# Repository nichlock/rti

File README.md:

# Open Source RTI

Source for the software, hardware and physical construction of a Reflectance Transformation Imager for George Washington University.

For information on the contents of the system, see [our Wiki](https://github.com/nichlock/rti/wiki). For more on the build and usage, [see the docs folder](../../tree/master/docs).

This repository contains our RTI's hardware and software implementation, and includes the source and documentation for:
1. A custom designed Arduino Mega shield to control the dome, which powers a three-color LED matrix and triggers the cameras.
2. Another custom circuit board which holds all three colors of LEDs in a smaller area than if we had three separate boards, allowing for a more compact dome.
3. The program to control the dome, with a serial or GUI control interface.
4. The GUI within the above program, which enables easy control over the whole system with no need for technical knowledge. See more about the GUI on our [system overview page](https://github.com/nichlock/rti/wiki/About-the-System#software-and-gui).

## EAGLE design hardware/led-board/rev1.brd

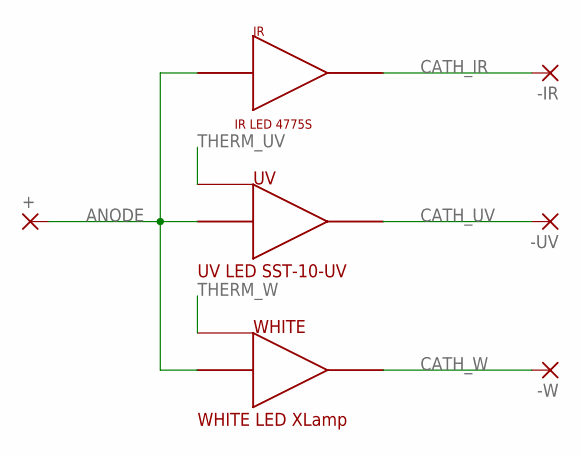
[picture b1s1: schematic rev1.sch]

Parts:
+: SMD5; SMD2,54-5,08
-IR: SMD5; SMD2,54-5,08
-UV: SMD5; SMD2,54-5,08
-W: SMD5; SMD2,54-5,08
IR: 4775S
UV: SST-10-UV; LED
WHITE: XLAMPXPG2; LED

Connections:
ANODE: +.1, IR.ANODE, IR.ANODE1 (ANODE), IR.ANODE2 (ANODE), UV.ANODE, WHITE.ANODE
CATH_IR: -IR.1, IR.CATHODE, IR.CATHODE1 (CATHODE)
CATH_UV: -UV.1, UV.CATHODE
CATH_W: -W.1, WHITE.CATHODE
THERM_UV: UV.THERM
THERM_W: WHITE.THERM

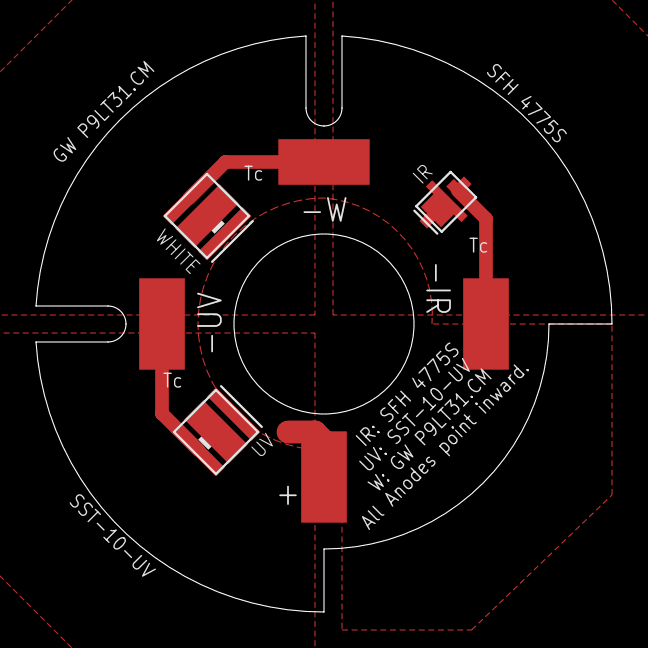
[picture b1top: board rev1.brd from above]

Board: 2 copper layers, 32.0 x 32.0 mm, 7 parts (0 on the bottom side), 4 nets.

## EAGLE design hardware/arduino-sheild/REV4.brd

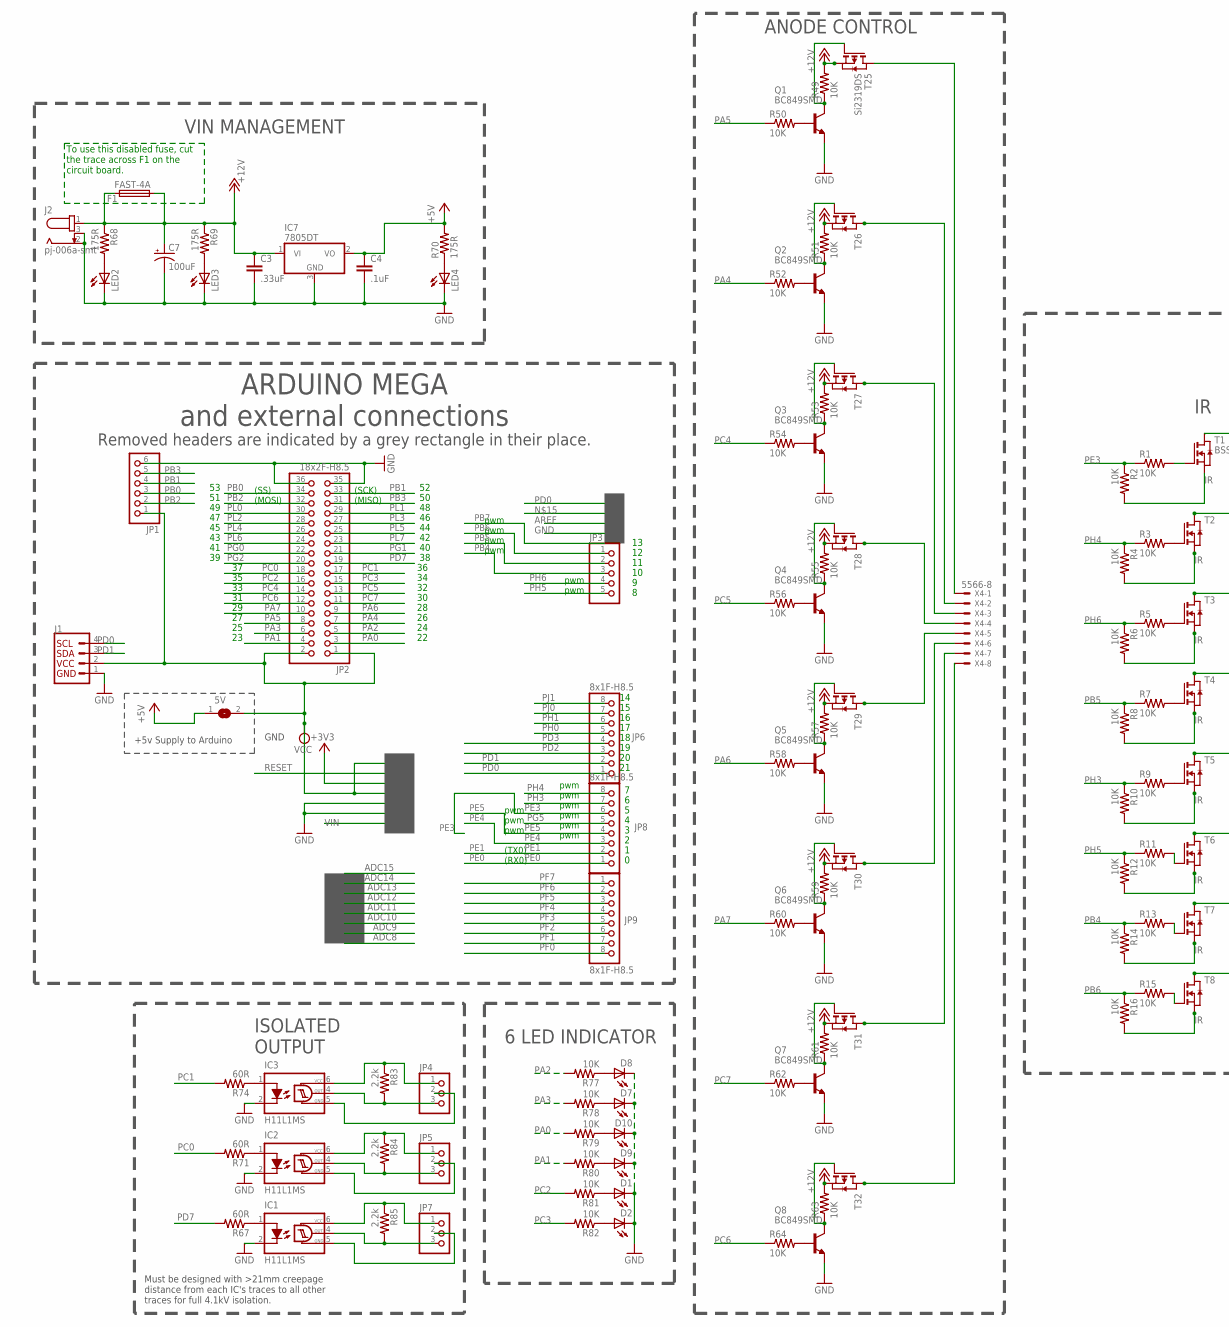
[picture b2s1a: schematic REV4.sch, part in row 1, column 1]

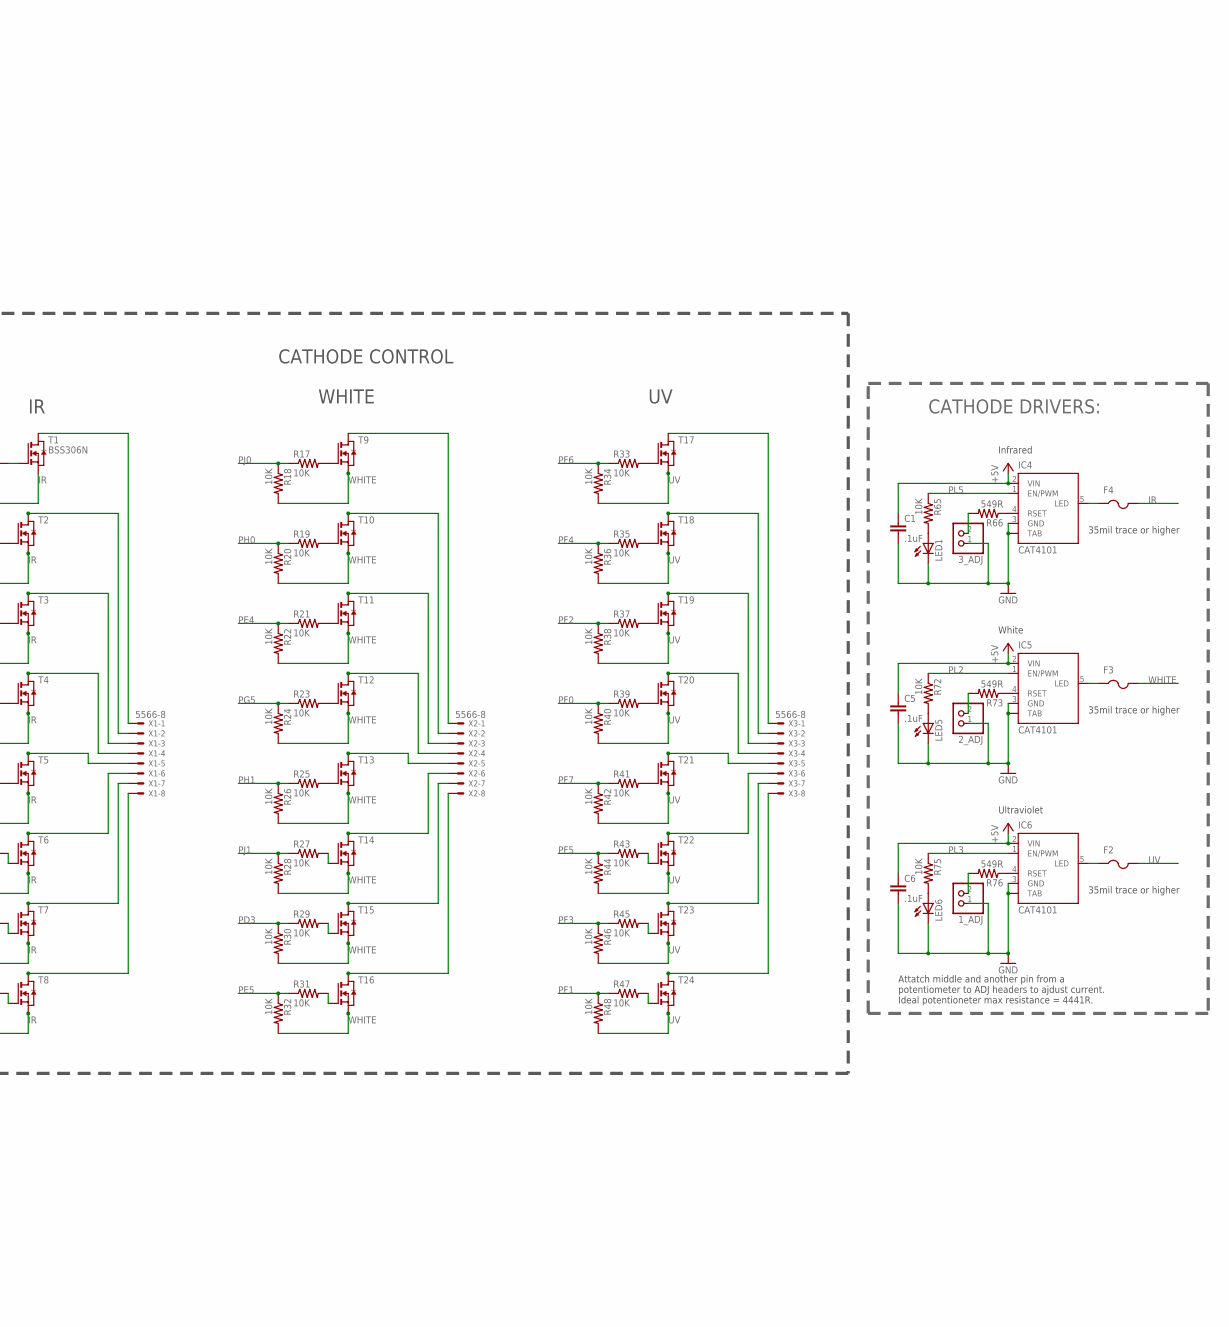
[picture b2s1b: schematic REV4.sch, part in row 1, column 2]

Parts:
1_ADJ, 2_ADJ, 3_ADJ: PINHD-1X2; 1X02
5V: SJ
C1, C4, C5, C6: .1uF; C0805
C3: .33uF; C0805
C7: 100uF; 153CLV-0807
D1, D2, D7, D8, D9, D10: LEDSMT1206; 1206
F1: FAST-4A; FUSE_MF-SMDF050
F2, F3, F4: PTCFUSE-1812; 1812
IC1, IC2, IC3: H11L1MS; DIL6-SMD
IC4, IC5, IC6: CAT4101; TO263_5
IC7: 7805DT; TO252
J1: I2C_STANDARD; 1X04
J2: pj-006a-smt; 69410X210102
JP1: PINHD-1X6; 1X06
JP2: 18x2F-H8.5; 2X18
JP3: PINHD-1X5; 1X05
JP4, JP5, JP7: PINHD-1X3; 1X03
JP6, JP8, JP9: 8x1F-H8.5; 1X08
LED1, LED2, LED3, LED4, LED5, LED6: LEDSMT1206; 1206
Q1, Q2, Q3, Q4, Q5, Q6, Q7, Q8: BC849SMD; SOT23-BEC
R1, R2, R3, R4, R5, R6, R7, R8, R9, R10, R11, R12, R13, R14, R15, R16, R17, R18, R19, R20, R21, R22, R23, R24, R25, R26, R27, R28, R29, R30, R31, R32, R33, R34, R35, R36, R37, R38, R39, R40, R41, R42, R43, R44, R45, R46, R47, R48, R49, R50, R51, R52, R53, R54, R55, R56, R57, R58, R59, R60, R61, R62, R63, R64, R65, R72, R75, R77, R78, R79, R80, R81, R82: 10K; R0805
R66, R73, R76: 549R; R0805
R67, R71, R74: 60R; R0805
R68, R69, R70: 175R; R0805
R83, R84, R85: 2.2k; R0805
T1: BSS306N; SOT-23
T2, T3, T4, T5, T6, T7, T8, T9, T10, T11, T12, T13, T14, T15, T16, T17, T18, T19, T20, T21, T22, T23, T24: NMOSSOT23; SOT-23
T25: Si2319DS; SOT-23
T26, T27, T28, T29, T30, T31, T32: PMOSSOT23; SOT-23
X1, X2, X3, X4: 5566-8

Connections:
+5V: 5V.1, C1.1, C4.1, C5.1, C6.1, IC4.2 (VIN), IC5.2 (VIN), IC6.2 (VIN), IC7.2 (VO), R70.2
+12V: C3.1, C7.+, F1.1, F1.2, IC7.1 (VI), J2.1, R49.2, R51.2, R53.2, R55.2, R57.2, R59.2, R61.2, R63.2, R68.1, R69.1, T25.2 (S), T26.2 (S), T27.2 (S), T28.2 (S), T29.2 (S), T30.2 (S), T31.2 (S), T32.2 (S)
GND: 1_ADJ.1, 2_ADJ.1, 3_ADJ.1, C1.2, C3.2, C4.2, C5.2, C6.2, C7.-, D1.C, D2.C, D7.C, D8.C, D9.C, D10.C, IC1.2 (C), IC2.2 (C), IC3.2 (C), IC4.3 (GND), IC4.TAB, IC5.3 (GND), IC5.TAB, IC6.3 (GND), IC6.TAB, IC7.3 (GND), J1.1, J2.2, J2.3, JP1.6, JP2.35, JP2.36, LED1.C, LED2.C, LED3.C, LED4.C, LED5.C, LED6.C, Q1.E, Q2.E, Q3.E, Q4.E, Q5.E, Q6.E, Q7.E, Q8.E
IR: F4.2, R2.2, R4.2, R6.2, R8.2, R10.2, R12.2, R14.2, R16.2, T1.2 (S), T2.2 (S), T3.2 (S), T4.2 (S), T5.2 (S), T6.2 (S), T7.2 (S), T8.2 (S)
unnamed: LED4.A, R70.1
unnamed: Q2.C, R51.1, T26.3 (G)
unnamed: T26.1 (D), X4.2
unnamed: 1_ADJ.2, R76.2
unnamed: Q1.B, R50.2
unnamed: Q1.C, R49.1, T25.3 (G)
unnamed: T25.1 (D), X4.1
unnamed: D8.A, R77.1
unnamed: 2_ADJ.2, R73.2
unnamed: LED2.A, R68.2
unnamed: Q2.B, R52.2
unnamed: F2.1, IC6.5 (LED)
unnamed: Q3.C, R53.1, T27.3 (G)
unnamed: D1.A, R81.1
unnamed: D7.A, R78.1
unnamed: T27.1 (D), X4.3
unnamed: D10.A, R79.1
unnamed: Q3.B, R54.2
unnamed: F3.1, IC5.5 (LED)
unnamed: Q4.C, R55.1, T28.3 (G)
unnamed: F4.1, IC4.5 (LED)
unnamed: T28.1 (D), X4.4
unnamed: 3_ADJ.2, R66.2
unnamed: Q4.B, R56.2
unnamed: IC4.4 (RSET), R66.1
unnamed: Q5.C, R57.1, T29.3 (G)
unnamed: IC5.4 (RSET), R73.1
unnamed: T29.1 (D), X4.5
unnamed: D2.A, R82.1
unnamed: Q5.B, R58.2
unnamed: Q6.C, R59.1, T30.3 (G)
unnamed: T30.1 (D), X4.6
unnamed: LED3.A, R69.2
unnamed: LED6.A, R75.2
unnamed: LED5.A, R72.2
unnamed: LED1.A, R65.2
unnamed: R1.2, T1.3 (G)
unnamed: D9.A, R80.1
unnamed: IC1.1 (A), R67.1
unnamed: IC2.1 (A), R71.1
unnamed: IC3.1 (A), R74.1
unnamed: Q6.B, R60.2
unnamed: T1.1 (D), X1.1
unnamed: R3.2, T2.3 (G)
unnamed: T2.1 (D), X1.2
unnamed: R5.2, T3.3 (G)
unnamed: T3.1 (D), X1.3
unnamed: R7.2, T4.3 (G)
unnamed: T4.1 (D), X1.4
unnamed: R9.2, T5.3 (G)
unnamed: T5.1 (D), X1.5
unnamed: R11.2, T6.3 (G)
unnamed: T6.1 (D), X1.6
unnamed: R13.2, T7.3 (G)
unnamed: T7.1 (D), X1.7
unnamed: R15.2, T8.3 (G)
unnamed: T8.1 (D), X1.8
unnamed: R17.2, T9.3 (G)
unnamed: T9.1 (D), X2.1
unnamed: R19.2, T10.3 (G)
unnamed: T10.1 (D), X2.2
unnamed: R21.2, T11.3 (G)
unnamed: T11.1 (D), X2.3
unnamed: R23.2, T12.3 (G)
unnamed: T12.1 (D), X2.4
unnamed: R25.2, T13.3 (G)
unnamed: T13.1 (D), X2.5
unnamed: R27.2, T14.3 (G)
unnamed: T14.1 (D), X2.6
unnamed: R29.2, T15.3 (G)
unnamed: T15.1 (D), X2.7
unnamed: R31.2, T16.3 (G)
unnamed: T16.1 (D), X2.8
unnamed: R33.2, T17.3 (G)
unnamed: T17.1 (D), X3.1
unnamed: R35.2, T18.3 (G)
unnamed: T18.1 (D), X3.2
unnamed: R37.2, T19.3 (G)
unnamed: T19.1 (D), X3.3
unnamed: R39.2, T20.3 (G)
unnamed: T20.1 (D), X3.4
unnamed: R41.2, T21.3 (G)
unnamed: T21.1 (D), X3.5
unnamed: R43.2, T22.3 (G)
unnamed: T22.1 (D), X3.6
unnamed: R45.2, T23.3 (G)
unnamed: T23.1 (D), X3.7
unnamed: R47.2, T24.3 (G)
unnamed: T24.1 (D), X3.8
unnamed: Q7.C, R61.1, T31.3 (G)
unnamed: T31.1 (D), X4.7
unnamed: Q7.B, R62.2
unnamed: Q8.C, R63.1, T32.3 (G)
unnamed: T32.1 (D), X4.8
unnamed: Q8.B, R64.2
OK6_GND: IC1.5 (GND), JP7.2
OK6_OUT: IC1.4 (OUT), JP7.3, R85.2
OK6_VCC: IC1.6 (VCC), JP7.1, R85.1
OK7_GND: IC2.5 (GND), JP5.2
OK7_OUT: IC2.4 (OUT), JP5.3, R84.2
OK7_VCC: IC2.6 (VCC), JP5.1, R84.1
OK8_GND: IC3.5 (GND), JP4.2
OK8_OUT: IC3.4 (OUT), JP4.3, R83.2
OK8_VCC: IC3.6 (VCC), JP4.1, R83.1
PA0: JP2.3, R79.2
PA1: JP2.4, R80.2
PA2: JP2.5, R77.2
PA3: JP2.6, R78.2
PA4: JP2.7, R52.1
PA5: JP2.8, R50.1
PA6: JP2.9, R58.1
PA7: JP2.10, R60.1
PB0: JP1.3, JP2.34
PB1: JP1.4, JP2.33
PB2: JP1.2, JP2.32
PB3: JP1.5, JP2.31
PB4: JP3.3, R13.1, R14.1
PB5: JP3.2, R7.1, R8.1
PB6: JP3.1, R15.1, R16.1
PC0: JP2.18, R71.2
PC1: JP2.17, R74.2
PC2: JP2.16, R81.2
PC3: JP2.15, R82.2
PC4: JP2.14, R54.1
PC5: JP2.13, R56.1
PC6: JP2.12, R64.1
PC7: JP2.11, R62.1
PD0: J1.4, JP6.1
PD1: J1.3, JP6.2
PD2: JP6.3
PD3: JP6.4, R29.1, R30.1
PD7: JP2.19, R67.2
PE0: JP8.1
PE1: JP8.2
PE3: JP8.6, R1.1, R2.1
PE4: JP8.3, R21.1, R22.1
PE5: JP8.4, R31.1, R32.1
PF0: JP9.8, R39.1, R40.1
PF1: JP9.7, R47.1, R48.1
PF2: JP9.6, R37.1, R38.1
PF3: JP9.5, R45.1, R46.1
PF4: JP9.4, R35.1, R36.1
PF5: JP9.3, R43.1, R44.1
PF6: JP9.2, R33.1, R34.1
PF7: JP9.1, R41.1, R42.1
PG0: JP2.22
PG1: JP2.21
PG2: JP2.20
PG5: JP8.5, R23.1, R24.1
PH0: JP6.5, R19.1, R20.1
PH1: JP6.6, R25.1, R26.1
PH3: JP8.7, R9.1, R10.1
PH4: JP8.8, R3.1, R4.1
PH5: JP3.5, R11.1, R12.1
PH6: JP3.4, R5.1, R6.1
PJ0: JP6.7, R17.1, R18.1
PJ1: JP6.8, R27.1, R28.1
PL0: JP2.30
PL1: JP2.29
PL2: IC5.1 (EN/PWM), JP2.28, R72.1
PL3: IC6.1 (EN/PWM), JP2.27, R75.1
PL4: JP2.26
PL5: IC4.1 (EN/PWM), JP2.25, R65.1
PL6: JP2.24
PL7: JP2.23
UV: F2.2, R34.2, R36.2, R38.2, R40.2, R42.2, R44.2, R46.2, R48.2, T17.2 (S), T18.2 (S), T19.2 (S), T20.2 (S), T21.2 (S), T22.2 (S), T23.2 (S), T24.2 (S)
UV_SET: IC6.4 (RSET), R76.1
VCC: 5V.2, J1.2, JP1.1, JP2.1, JP2.2
WHITE: F3.2, R18.2, R20.2, R22.2, R24.2, R26.2, R28.2, R30.2, R32.2, T9.2 (S), T10.2 (S), T11.2 (S), T12.2 (S), T13.2 (S), T14.2 (S), T15.2 (S), T16.2 (S)

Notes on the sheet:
pwm
(TX0)
(RX0)
(SS)
(MOSI)
(SCK)
(MISO)
ARDUINO MEGA and external connections
35mil trace or higher
CATHODE DRIVERS:
ISOLATED OUTPUT
ANODE CONTROL
Infrared
White
Ultraviolet
CATHODE CONTROL
GND
Must be designed with >21mm creepage distance from each IC's traces to all other traces for full 4.1kV isolation.
VIN MANAGEMENT
6 LED INDICATOR
Attatch middle and another pin from a potentiometer to ADJ headers to ajdust current. Ideal potentioneter max resistance = 4441R.
+5v Supply to Arduino
Removed headers are indicated by a grey rectangle in their place.
To use this disabled fuse, cut the trace across F1 on the circuit board.
WHITE

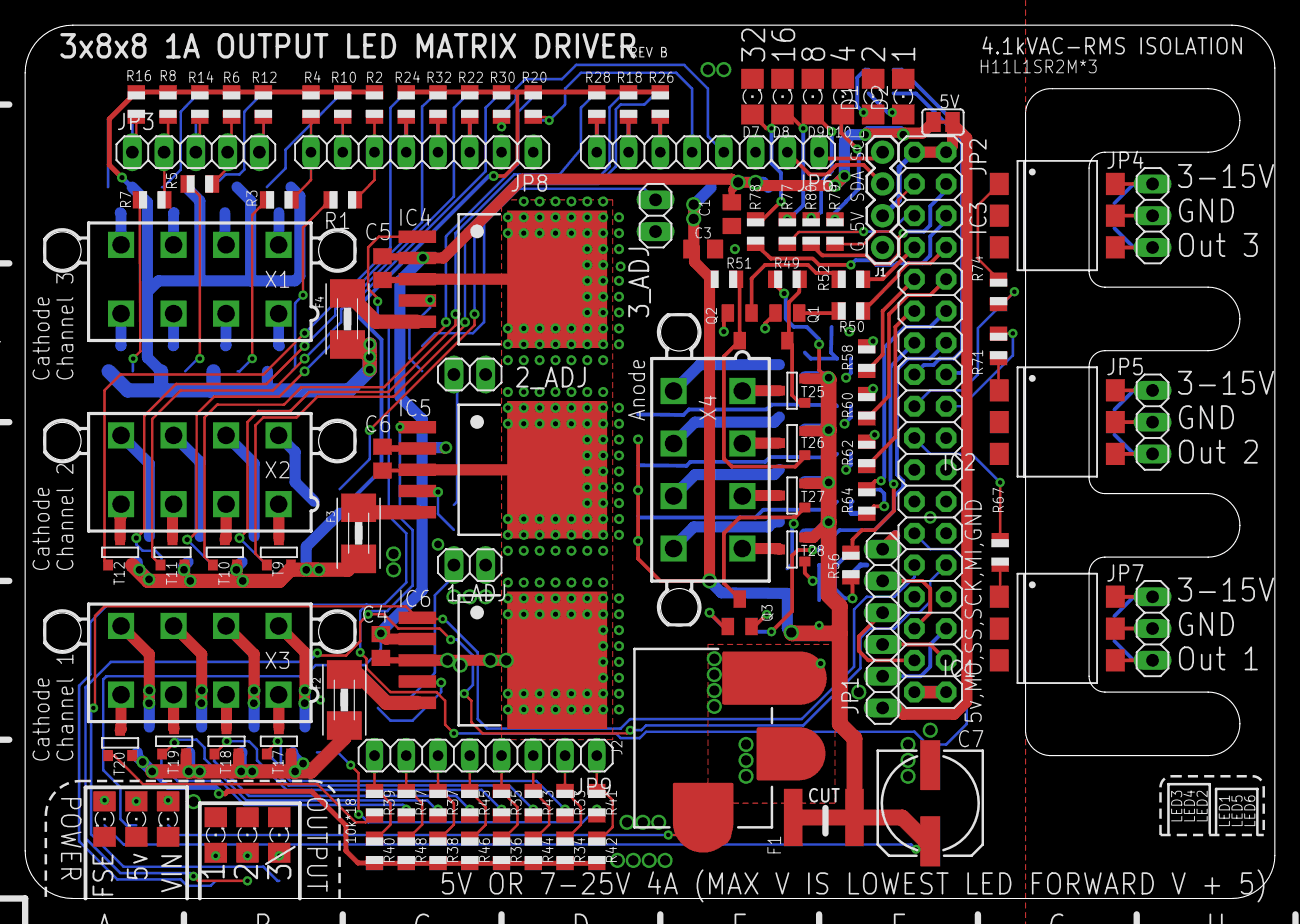
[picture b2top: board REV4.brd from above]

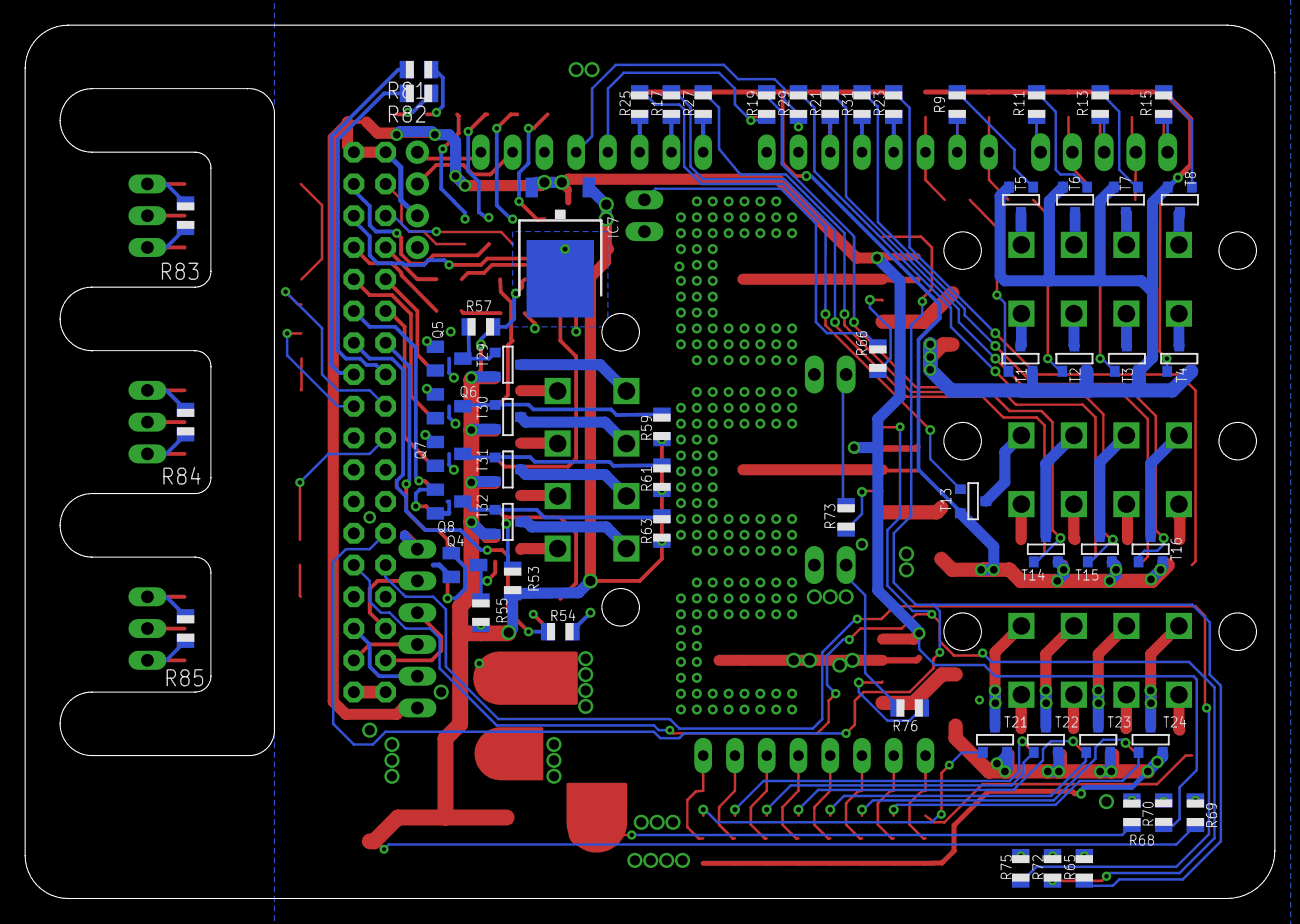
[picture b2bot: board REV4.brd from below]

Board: 2 copper layers, 99.9 x 69.8 mm, 173 parts (59 on the bottom side), 162 nets.

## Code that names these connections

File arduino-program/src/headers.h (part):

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#include <MemoryFree.h>

/*~~~~~PER-USE SETTINGS~~~~~*/
#define USE_ALT_PIN_SETUP // Uses PD2 in place of PD3 due to an error on the
                          // board. DISABLE IN RELEASE!

#define DEFAULT_BAUD_RATE 115200 // Sets the default baud rate
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
// Default channel names for display and serial communication use.
#define DEFAULT_CHANNEL_NAME_1 "Ultra Vt"
#define DEFAULT_CHANNEL_NAME_2 "White"
#define DEFAULT_CHANNEL_NAME_3 "InfraRed"

#define CHANNEL_NAME_MAX_CHARACTERS 8 // Should be left at 8, since some boxes
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 * Thus _BV(PX3) would be 0x08 or 0b00001000. */

/*~~~~~ARRAY INFO~~~~~
 * Row Pins 1-8: PA5, PA4, PC4, PC5, PA6, PA7, PC7, PC6.
 * Channel 1 Pins 1-8: PF6, PF4, PF2, PF0, PF7, PF5, PF3, PF1
 * Channel 2 Pins 1-8: PJ0, PH0, PE4, PG5, PH1, PJ1, PD3, PE5
 * Channel 3 Pins 1-8: PE3, PH4, PH6, PB5, PH3, PH5, PB4, PB6
 */
#define RR(x)                                                                  \
	((x == 0)                                                                    \
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	                   : PORTC))))))) // Row
// register
// for #
// Row Pins 1-8: PA5, PA4, PC4, PC5, PA6, PA7, PC7, PC6.
#define RB(x)                                                                  \
  \
	((x == 0)                                                                      \
	 ? PA5                                                                    \
	 : ((x == 1)                                                              \
	    ? PA4                                                             \
	    : ((x == 2)                                                       \
	       ? PC4                                                      \
	       : ((x == 3)                                                \
	          ? PC5                                               \
	          : ((x == 4)                                         \
	             ? PA6                                        \
	             : ((x == 5)                                  \
	                ? PA7                                 \
	                : ((x == 6) ? PC7 : PC6))))))) // Row
                                                 // bits
                                                 // for
                                                 // #x
// Channel 1 Pins 1-8: PF6, PF4, PF2, PF0, PF7, PF5, PF3, PF1
#define CH1R(x)                                                                \
	((x == 0)                                                                    \
	 ? PORTF                                                                 \
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// for #x
#define CH1B(x)                                                                \
	((x == 0)                                                                    \
	 ? PF6                                                                   \
	 : ((x == 1)                                                             \
	    ? PF4                                                            \
	    : ((x == 2)                                                      \
	       ? PF2                                                     \
	       : ((x == 3)                                               \
	          ? PF0                                              \
	          : ((x == 4)                                        \
	             ? PF7                                       \
	             : ((x == 5)                                 \
	                ? PF5                                \
	                : ((x == 6) ? PF3                    \
	                   : PF1))))))) // Channel
                                  // 1 Bit
                                  // for
                                  // #x.
// Channel 2 Pins 1-8: PJ0, PH0, PE4, PG5, PH1, PJ1, PD3, PE5

#ifdef USE_ALT_PIN_SETUP // Uses alternative pins due to a fault on the
                         // origional prototype
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	#define CH2B(x)                                                                \
    \
	((x == 0)                                                                      \
	 ? PJ0                                                                    \
	 : ((x == 1)                                                              \
	    ? PH0                                                             \
	    : ((x == 2)                                                       \
	       ? PE4                                                      \
	       : ((x == 3)                                                \
	          ? PG5                                               \
	          : ((x == 4)                                         \
	             ? PH1                                        \
	             : ((x == 5) ? PJ1                            \
	                : ((x == 6) ? PG2 : PE5)))))))

	#else /* ifdef USE_ALT_PIN_SETUP */

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#define CH2B(x)                                                                \
  \
	((x == 0)                                                                      \
	 ? PJ0                                                                    \
	 : ((x == 1)                                                              \
	    ? PH0                                                             \
	    : ((x == 2)                                                       \
	       ? PE4                                                      \
	       : ((x == 3)                                                \
	          ? PG5                                               \
	          : ((x == 4)                                         \
	             ? PH1                                        \
	             : ((x == 5) ? PJ1                            \
	                : ((x == 6) ? PD3 : PE5)))))))
#endif /* ifdef USE_ALT_PIN_SETUP */

// Channel 3 Pins 1-8: PE3, PH4, PH6, PB5, PH3, PH5, PB4, PB6
#define CH3R(x)                                                                \
	((x == 0)                                                                    \
	 ? PORTE                                                                 \
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#define CH3B(x)                                                                \
  \
	((x == 0)                                                                      \
	 ? PE3                                                                    \
	 : ((x == 1)                                                              \
	    ? PH4                                                             \
	    : ((x == 2)                                                       \
	       ? PH6                                                      \
	       : ((x == 3)                                                \
	          ? PB5                                               \
	          : ((x == 4)                                         \
	             ? PH3                                        \
	             : ((x == 5) ? PH5                            \
	                : ((x == 6) ? PB4 : PB6)))))))

#define SR(x)                                                                  \
	((x == 0) ? PORTG : ((x == 1) ? PORTC : PORTC)) // Shutter registers
#define SB(x) ((x == 0) ? PG0 : ((x == 1) ? PC0 : PC1)) // Shutter bits

#define ENR(x)                                                                 \
	((x == 0) ? PORTL                                                            \
	 : ((x == 1) ? PORTL : PORTL)) // Enable register for a channel
#define ENB(x) ((x == 0) ? PL3 : ((x == 1) ? PL2 : PL5)) // Enable pin bits
// Binary LED readout pins
#define BIR(x)                                                                 \
	((x == 0)                                                                    \
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	             : PORTC)))))
#define BIB(x)                                                                 \
	((x == 0)                                                                    \
	 ? PA3                                                                   \
	 : ((x == 1)                                                             \
	    ? PA2                                                            \
	    : ((x == 2) ? PA1 : ((x == 3) ? PA0 : ((x == 4) ? PC2 : PC3)))))

/*~~~~~main.cpp~~~~~*/
bool advancedDelay(unsigned long time, bool shutterHigh = false,
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// table)
// Each requires 8 bytes. (8 bytes x 8 bits/byte == 64 led bits)
#define USABLE_IR_ARRAY 702 // Usable IR LEDs as bits
#define USABLE_WHITE_ARRAY 710 // Usable White LEDs
#define USABLE_UV_ARRAY 718 // Usable UV LEDs // Ends at byte 726
// These take the LED #1-64 as an input
#define READ_BIT_USABLE_ARRAY(x, y) bitRead(EEPROM.read(USABLE_IR_ARRAY + (x / \
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
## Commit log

2020-08-10 Initial commit with files
2020-08-11 Update README.md
    Started documentation of boards
2020-08-12 Added warped image, must be updated!
2020-08-12 Delete led-array.md
    Moved to wiki
2020-08-12 Delete code.md
    Moved to wiki
2020-08-12 Delete construction.md
    Moved to wiki
2020-08-12 Delete led-board.md
    Moved to wiki
2020-08-12 Create dome
2020-08-12 Add dome images via upload
2020-09-02 Change newlines

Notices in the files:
parts and their libraries:
Wurth_Elektronik_Electromechanic_DC_Powe: Copyright: Würth Elektronik
SparkFun-Connectors: Licensing: Creative Commons ShareAlike 4.0 International - https://creativecommons.org/licenses/by-sa/4.0
